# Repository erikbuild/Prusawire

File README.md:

# Prusawire 2025.B1

An unofficial Prusa MK3 and MK4 total conversion mod, from Positron's April Fools of 2025.

## Current Release

Beta 1 (2025.B1) was released on 2025-08-21.  There have been [updates and improvements since then](CHANGELOG.md).  Be sure to grab the latest STLs and documentation from the GitHub Repository.

Release 1 (2026.R1) is coming SOON(tm)!

Link to Beta 1 CAD Viewer: [Link](https://positron3d.autodesk360.com/g/shares/SH30dd5QT870c25f12fc28f5f9169dbff2f2)

Link to instructions for gantry de-racking & installing XZ and Y belts: [Link](https://prusawire.positron3d.com/hardware/)

## About

> Nomad of Positron3D came up with this idea shortly after completing their Switchwire build. The idea started as a quick design exercise, to try and convert a Prusa MK4S frame into a Switchwire, using everything left over from a CORE One Upgrade.
>
> As the first iteration wrapped up, I took interest in the project, and decided to take this April Fools joke one step further and build it into a reliable machine.
>
> After months of hard work, please enjoy the build ❤
> 
> -@ellafoxo

## Who This Printer is For

Pick one of the following:

- You have an old MK3, MK3S, or MK3S+, and you want to teach an old dog new tricks and are on a budget
- You upgraded from MK4S to a Core ONE, and have a leftover frame. You are okay spending money on building a new printer with that hardware.

Additionally, the following says this printer is for you: 

- You want to take your first steps into RepRap beyond Prusa, and Voron is an exciting route.
- You are comfortable working from a CAD file as your build guide
- You respect the Frankenstein-y nature of this April Fools joke printer

## Want to Support the Project?

First of all, thank you! Development costs have been mostly self-funded, with filament sponsored by Levendigs, and LDO Motors for providing the funds for the Prusa MK4 frame.

- Support Positron3D to fund future endeavors: 
   - [Donate to Positron3D](https://www.paypal.com/donate/?hosted_button_id=YGPRVTSHN4FQG)
   - [Positron3D Merch](https://nomadsgalaxy-shop.fourthwall.com/)

## Build Volume

X: 250mm
Y: 210mm
Z: 185mm

## Bill of Materials

[Prusawire 2025.B1 Bill of Materials](BOM/BOM_2025-B1.md)

## Technical Support

Prusawire, technically, does not count as a Voron Switchwire. We ask you kindly not to nag the Voron Design team for technical support.

Instead, please [join the Positron3D Discord](https://discord.gg/positron) for support with your build, and maybe share your progress over there too.

## Serial Numbers

We are accepting serials over on the [Positron 3D Discord](https://discord.gg/positron). Please submit your request to the #prusawire-serial-request channel over there. 

## Upgrading the Einsy Rambo to Klipper - Read this

Installing Klipper on the Einsy Rambo board is possible, with extra steps. Follow the guide [published by the awesome folks at MyRigs3D](https://myrigs3d.com/blogs/infos/revive-your-prusa-mk3s-with-klipper-1-5-flash-bootloader)! We recommend Method 2.

**Note:** Some users have reported problems using `avrdude` with the latest Raspberry Pi OS version (bookworm). If you experience error messages from avrdude complaining about gpio ports being busy, please try using the bullseye version of Raspberry Pi OS instead, available as "Raspberry Pi OS (Legacy)" in Raspberry Pi Imager.

## Klipper Configuration Files

The most up–to–date Klipper configuration files for setting up or updating the Prusawire are in our [config repository](https://github.com/Positron3D/prusawire-klipper-config).

## Credits 

Many thanks to all the awesome people and companies that have made this possible. Notably:

Most importantly:
- Ella Fox, _the architect of Beta 1_ - who took Prusawire from a joke to a beautiful and powerful machine. [Buy Ella a Ko-Fi](https://ko-fi.com/ellafoxo)

And also:
- Prusa Research - Cheers, Josef and the team for the MK3/4 platform on which this was built upon!
- Voron Design - Switchwire

- Positron 3D Team - Too many to name, you know who you are <3
- Early development team:
   - Nomad's Galaxy
   - Koosh
   - Birb
- Jason @ LDO Motors - Part sponsorship
- Levendigs - Part sponsorship 
- Early access testers:-
   - Killa_Prints
   - LinksLab
   - Safe
   - Silicon
   - TheNexusAvenger
   - torsten
- Contributors since Beta 1
   - einarjh
   - erikbuild

## Extra Credits for Existing Printed Parts

See the collection for the most up to date! To name them:

- Printable M3 T-Nuts for 3030 Extrusion, by Kapplion
- Stealthburner umbilical strain relief, by nagelwerkstatt

## Team

Prusawire is currently maintained by the Positron 3D Team.

- Design Lead: @Safe-ty
- Documentation Lead: @erikbuild
- Software Lead: @TheNexusAvenger

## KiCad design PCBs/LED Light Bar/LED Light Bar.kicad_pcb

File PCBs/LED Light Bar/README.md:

# Prusawire Daylight Stick by Ella Fox

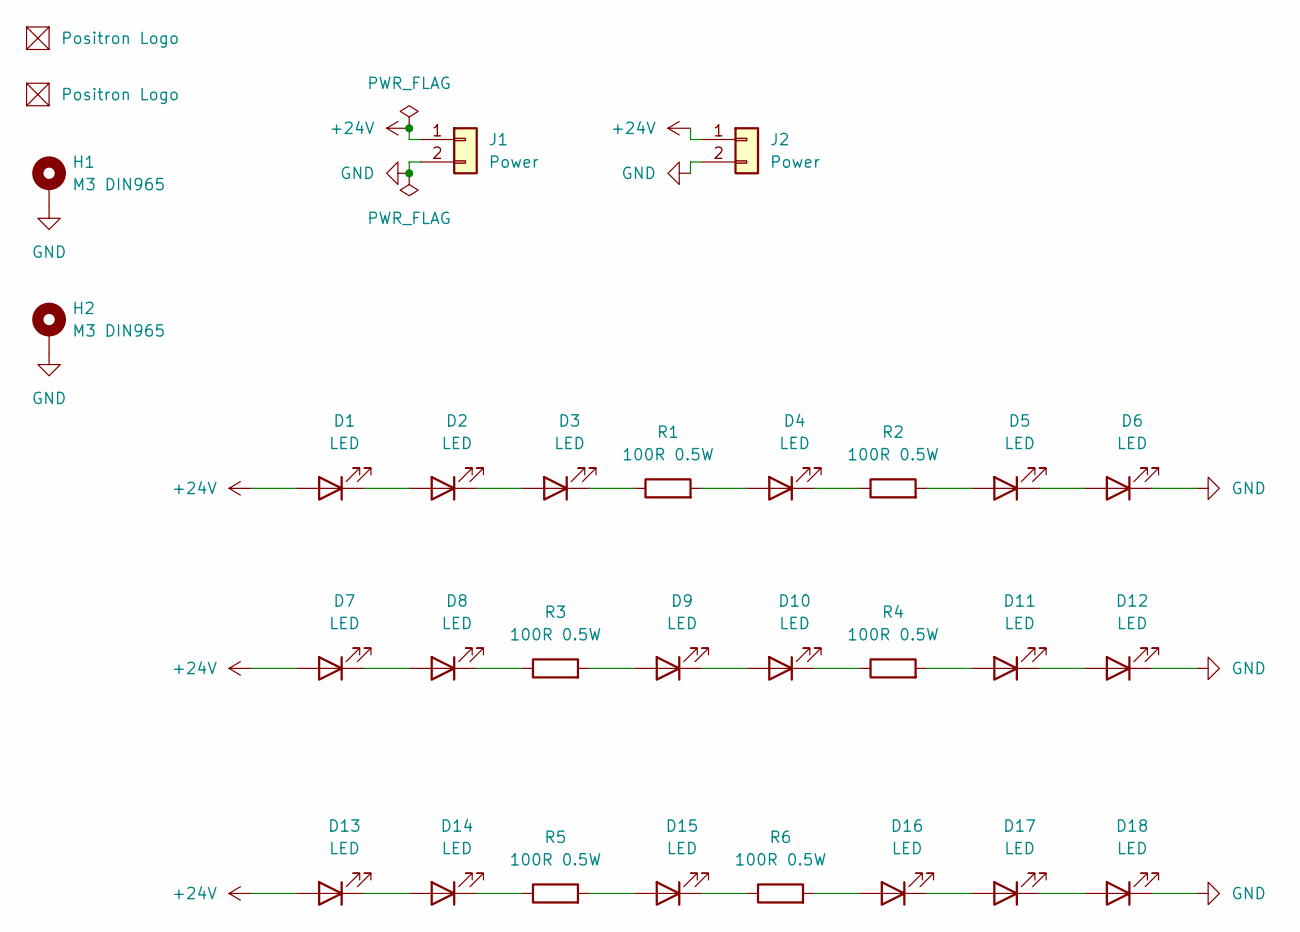
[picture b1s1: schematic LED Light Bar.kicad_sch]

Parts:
D1, D2, D3, D4, D5, D6, D7, D8, D9, D10, D11, D12, D13, D14, D15, D16, D17, D18: LED; LED_PLCC_2835_Handsoldering; LCSC C182223
H1, H2: M3 DIN965; MountingHole_3.2mm_M3_Pad_Via
J1, J2: Power; JST_XH_S2B-XH-A_1x02_P2.50mm_Horizontal
R1, R2, R3, R4, R5, R6: 100R 0.5W; R_1210_3225Metric_Pad1.30x2.65mm_HandSolder; LCSC C137089
S1, S2: Positron_Logo

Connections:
+24V: D1.2 (A), D7.2 (A), D13.2 (A), J1.1, J2.1
GND: D6.1 (K), D12.1 (K), D18.1 (K), H1.1, H2.1, J1.2, J2.2
unnamed: D1.1 (K), D2.2 (A)
unnamed: D2.1 (K), D3.2 (A)
unnamed: D3.1 (K), R1.1
unnamed: D4.2 (A), R1.2
unnamed: D4.1 (K), R2.1
unnamed: D5.2 (A), R2.2
unnamed: D5.1 (K), D6.2 (A)
unnamed: D7.1 (K), D8.2 (A)
unnamed: D8.1 (K), R3.1
unnamed: D9.2 (A), R3.2
unnamed: D9.1 (K), D10.2 (A)
unnamed: D10.1 (K), R4.1
unnamed: D11.2 (A), R4.2
unnamed: D11.1 (K), D12.2 (A)
unnamed: D13.1 (K), D14.2 (A)
unnamed: D14.1 (K), R5.1
unnamed: D15.2 (A), R5.2
unnamed: D15.1 (K), R6.1
unnamed: D16.2 (A), R6.2
unnamed: D16.1 (K), D17.2 (A)
unnamed: D17.1 (K), D18.2 (A)

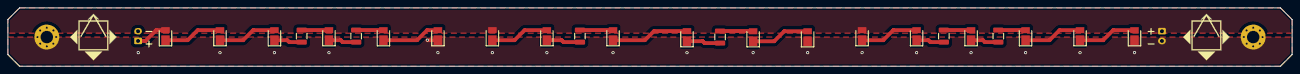
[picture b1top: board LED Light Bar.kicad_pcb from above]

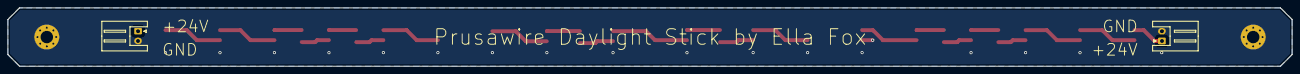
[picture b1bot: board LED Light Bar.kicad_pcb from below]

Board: 2 copper layers, 330.0 x 15.0 mm, 30 parts (2 on the bottom side), 23 nets.

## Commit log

2025-08-21 Prusawire 2025.B1
2025-08-21 We're GPLv3.
2025-08-21 Remove beta observations (now resolved)
2025-09-04 Add custom sponsorship URL to FUNDING.yml
2025-09-06 Update README.md (#1)
    Updated README to add link to Klipper Config page
2025-09-13 Add Anthead Toolhead Manual
    Add pdf from https://github.com/PrintersForAnts/AntHead.git
2025-09-13 Prusawire Serial Sticker Template (#2)
    * Create README.md
    * Add files via upload
    * Rename Serial Sticker/prusawire_serial_sticker_template_V2_inkscape.svg to Serial Sticker/Inkscape/prusawire_serial_sticker_template_V2_inkscape.svg
    * Create Del
    * Delete Serial Sticker/Affinity Designer 2/Del
    * Add files via upload
2025-09-16 Initial documentation of the gantry deracking process. (#4)
    * Initial documentation of the gantry deracking process.
    * Typo.
2025-09-17 Formatting fixes for Gantry Deracking doc (#5)
    * Initial documentation of the gantry deracking process.
    * Typo.
    * Fixed formatting.
    * Added alt-text.
    * Formating tweaks++
2025-09-19 XZ Belt Install and Tensioning Documentation (#6)
    * Initial documentation of the gantry deracking process.
    * Typo.
    * Fixed formatting.
    * Added alt-text.
    * Formating tweaks++
    * XZ Belt Installation and Tensioning
2025-09-22 Added quick listing of popular mods.
2025-11-02 Fixed a typo and updated Mods list.
2025-11-02 Typos
2025-11-02 Added XZ Belt Reroute mod + TPU Feet
2025-11-05 Update the README further.
2025-11-12 First attempt at tweaks to y_belt_tensioner. tensioner_front has recess for socket cap to allow for 5-6mm of adjustment as well as R1 embossed text. tensioner_rear in both V0SN and M3S nut versions (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
2025-11-16 Remove old rear tensioner STL.
2025-11-24 Fix typo in filename: [a]_x_motor_mount_b.stl
2026-02-17 Enhance tuning calibration resources and guidelines
    Added resources for calibration and tuning, including links to various guides and tools. Updated the prioritization of calibration steps.
2026-03-14 Create PrusaSlicer profile generator. (#73)
2026-05-01 Squash 55 CAD/design commits into single history checkpoint. There are a ... lot... of binary CAD files here.
    ### e7ad8cf I don't even know anymore.
    Author: erikbuild
    Date: Fri May 1 12:49:18 2026 -0400
    ### 3575dc9 Final CAD Files
    Author: Safe
    Date: Thu Apr 30 19:57:53 2026 -0400
2026-05-01 ERIK FORGOT THE STLs LOL oh and also...
    Squash 55 CAD/design commits into single history checkpoint. There are a ... lot... of binary CAD files here.
    ### e7ad8cf I don't even know anymore.
    Author: erikbuild
    Date: Fri May 1 12:49:18 2026 -0400
    ### 3575dc9 Final CAD Files
    Author: Safe
2026-05-07 Final Cad Edits
    Added bearing pads and reworked the caps to include small sections of VHB
    Erik is a bad infuence. Dont listen to him or HartK or Chaz or Iamus or Pooh or Matt Chu or scope creep. they keep pointing out issues with models and now i need to fix them
2026-05-08 Minor fix to supports for xz_end_clips. This is entirely the fault of MakerPhil.
2026-05-09 commit 0199b2c0275c2a37f9fcd3e9ef5f8c06d02c5cbc Author: Safe Date: Sat May 9 11:21:24 2026 -0400
    The Final Final Cad
    Based on the previous modifications, the final cad has been updated
    commit e7e7080ab59a8c9a549bd24cfe83959b676c96fb
    Author: Safe
    Date: Sat May 9 11:19:57 2026 -0400
    More Final Cad Fixes
2026-05-11 Author: Safe Date: Sun May 10 22:21:00 2026 -0400
    Updates to Bearing Fitment
    Thanks to Nexus, some issues needed fixed meaning the previous version of the cad needed to be updated.
2026-05-15 commit 3cf6c82ec7c801166356d2831ac792b70d7245c1 (HEAD -> main) Author: Safe <169000330+Safe-ty@users.noreply.github.com> Date: Thu May 14 22:23:12 2026 -0400
    Add Finishing Touches
    readded some missing features
    Thanks to the observations of Nomad, we needed more memes to the final cad.
    Co-Authored-By: Erik Reynolds <23739+erikbuild@users.noreply.github.com>
    commit 994fc2581d3f23930caecc61cd797f68a1f8ef8e
    Author: Safe <169000330+Safe-ty@users.noreply.github.com>
2026-05-16 ... whoops
2026-05-25 commit 0fb8c268dcefaa50c8ef9c5413df01f0ae00ec30 (HEAD, main) Author: Safe <169000330+Safe-ty@users.noreply.github.com> Date: Sun May 24 11:48:57 2026 -0400
    The Final CAD V67
    Is this the final cad? only fried of the project clee knows
    commit ed4346c117acda4473f67b3e5d6df8433b846215
    Author: Safe <169000330+Safe-ty@users.noreply.github.com>
    Date: Sun May 24 11:47:49 2026 -0400
    Double Shear for Prusawire
2026-06-05 Reorganize Double Shear and Y_Axis files into motor/variant subfolders
    why does Safe use windows if not to make my life more difficult.
2026-06-05 commit 496faa4c0122f9d3e5722a3c19a27d08cf0fab16 (HEAD -> main) Author: Safe <169000330+Safe-ty@users.noreply.github.com> Date: Thu Jun 4 10:46:08 2026 -0400
    Fix Residual Belt Issues
    Thanks to Erik Build and Scope Creep, the cad has been updated to include toothed belts in cad.
    commit cf14391fe3bc0f0b0e8b55eac56a32a0837a6e23
    Author: Safe <169000330+Safe-ty@users.noreply.github.com>
    Date: Wed Jun 3 22:18:41 2026 -0400
    Add Finishing Touches
2026-06-06 Author: Safe <169000330+Safe-ty@users.noreply.github.com> Date: Fri Jun 5 22:40:31 2026 -0400
    More Yaxis Updates
    Thanks for the request Nexus. Good thing Erik needs to reprocess the files 😆
2026-06-12 manwel
2026-06-15 BOM tweaks from the one true @joescalon
